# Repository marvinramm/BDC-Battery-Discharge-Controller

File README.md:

# BDC – Battery Discharge Controller

**Brings charged Li-Po and Li-Ion packs (2S–6S) down to storage voltage quickly. You set the target voltage per cell on the device. The BDC switches the load and stops on its own when the target is reached. An ESP32 runs its own firmware, BDC OS: it shows the progress on an OLED and streams it over Bluetooth LE.**

In RC model building, packs are often charged and then not used. A full Li-Po left for days ages fast; it should sit at about 3.8 V per cell. Most chargers discharge with only a few watts. The BDC uses a real load instead and gets a pack to storage voltage much faster. The first revision carried that load on the board. The second one switches any external load up to 15 A.

## Features

- **2S to 6S Li-Po / Li-Ion:** the number of cells is detected from the pack voltage at start-up.
- **Adjustable target voltage:**
  - 3.60–3.90 V per cell in 0.05 V steps, 3.75 V by default
  - the load switches off automatically when the target is reached
- **Accurate measurement:**
  - the load is switched off briefly for every reading, so the voltage drop under load does not falsify the result
  - the ADC is linearised with a calibration table
- **One-button operation (REV2):**
  - short press changes the target voltage
  - long press starts or stops the discharge
  - an RGB LED shows the state: idle, discharging, done
- **0.96" OLED:**
  - cell voltage, pack voltage, distance to the target, progress in percent
  - Bluetooth status and the detected cell count
- **Bluetooth LE:** all values are sent as notifications, so a phone app can show the progress.
- **Buzzer** when the pack is done, then **light sleep** after one minute without input.

## How it works

```mermaid
flowchart LR
    BAT["Battery<br/>2S–6S"] -- XT60 --> SW["P-MOSFET switch<br/>AOD403"]
    SW -- XT60 --> LOAD["External load<br/>up to 15 A"]
    BAT --> DIV["Voltage divider"] --> ESP["ESP32<br/>BDC OS"]
    BAT --> LDO["LM2937<br/>3.3 V"] --> ESP
    ESP -- DISCHARGE_ON --> SW
    ESP <--> OLED["OLED<br/>I²C"]
    BTN["Button"] --> ESP
    ESP --> UI["RGB LED · buzzer"]
    ESP <-. BLE .-> APP["Phone"]
```

The ESP32 measures the pack voltage through a voltage divider and averages 100 samples. During the reading it switches the load off for a moment. BDC OS converts the reading to a voltage with a measured calibration table and divides it by the detected number of cells. As long as the average cell voltage is above the target, the MOSFET stays on. When it drops 20 mV below the target, the BDC switches off, beeps and shows "Done".

## Revisions

| | REV1 (2022) | REV2 (2023) |
|---|---|---|
| **Concept** | All-in-one: load, balancer and cell monitoring on one board | Compact controller that switches an external load |
| **Load** | 100 W / 8 Ω aluminium resistor on the board, cooled by a 40 mm fan | Any load on the second XT60 connector, up to 15 A |
| **Balancing** | Six HY2213 balancer channels with 62 Ω bleed resistors | – |
| **Measurement** | Every cell via the balancer connector and a CD74HC4067 multiplexer; current and power with an INA219 and a 10 mΩ shunt | Pack voltage via voltage divider |
| **Operation** | Rotary encoder with push button | One button |
| **Connectors** | XT60, XT30, balancer connector (up to 6S), fuse holders | 2 × XT60 |
| **Board** | 100.4 × 89.4 mm | 76.7 × 38.9 mm |
| **Firmware** | [BDC OS 0.4](firmware/BDC-OS-REV1) (prototype) | [BDC OS 0.5.3](firmware/BDC-OS) |

With a fixed 8 Ω resistor, the discharge current of REV1 depends on the pack voltage: about 1 A at 2S, about 3 A at 6S. For large packs that is slow, and the resistor needs active cooling. REV2 leaves out the load. You connect whatever fits the pack, e.g. a power resistor or an electronic load. The board itself becomes small enough for a 3D-printed or acrylic case.

## Repository layout

```
firmware/BDC-OS/          BDC OS 0.5.3 for REV2 (Arduino sketch)
firmware/BDC-OS-REV1/     BDC OS 0.4 for REV1 (prototype)
hardware/bdc-rev1/        Schematic (PDF), BOM, ESP32 pin assignment, EAGLE source
hardware/bdc-rev2/        Schematic (PDF), BOM, ESP32 pin assignment, EAGLE source
hardware/mechanical/      3D-printed parts
docs/images/              Pictures used in this README
```

Gerber files and ready-to-flash firmware images are attached to the [releases](https://github.com/marvinramm/BDC/releases). Libraries, build settings and the Bluetooth interface are described in [`firmware/README.md`](firmware/README.md).

> [!WARNING]
> The BDC handles batteries that can deliver very high currents. Fuse the battery line, watch the temperature of the load and never leave a discharging pack unattended.

## License

© 2022–2023 Marvin Ramm. Open source with attribution:

- Code (`firmware/`): [MIT](LICENSE)
- Hardware and documentation: [CC BY 4.0](hardware/LICENSE)

Commercial use is allowed. Credit "BDC by Marvin Ramm" with a link to this repository. Details are in [LICENSING.md](LICENSING.md).

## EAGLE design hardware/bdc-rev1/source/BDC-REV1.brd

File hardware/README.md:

# Hardware

| Folder | Content |
|---|---|
| [`bdc-rev1`](bdc-rev1) | REV1 (2022): schematic (PDF, 2 sheets), BOM, ESP32 pin assignment, EAGLE schematic and board in `source/` |
| [`bdc-rev2`](bdc-rev2) | REV2 (2023): schematic (PDF), BOM, ESP32 pin assignment, EAGLE schematic and board in `source/` |
| [`mechanical`](mechanical) | `encoder_knob_rev1.stl` for the rotary encoder of REV1, `protection_cap.stl` |

The Gerber, drill and pick-and-place files of both revisions are attached to the [releases](https://github.com/marvinramm/BDC/releases).

- **REV2:** the files come from the EAGLE CAM processor.
- **REV1:** no CAM output was left, so the files were generated from the EAGLE board with KiCad's EAGLE importer. Check them in a Gerber viewer before you order.

The EAGLE files use parts from my own libraries. EAGLE embeds them in the `.sch` / `.brd` files, so the designs open without the libraries.

## REV1 – all-in-one

Battery input via XT60 and balancer connector (up to 6S). Each cell has an HY2213 balancer IC that switches a 62 Ω bleed resistor. The cell voltages go through dividers to a CD74HC4067 multiplexer and on to the ESP32 ADC. An INA219 measures current and power across a 10 mΩ shunt. An AOD403 P-MOSFET switches the 100 W / 8 Ω aluminium resistor on top of the board, and a 40 mm fan cools it.

## REV2 – controller for an external load

Battery and load each connect to an XT60 (`OUTPUT 15A` on the silkscreen). An AOD403 P-MOSFET, driven by an SI2302, switches the load on the high side. An LM2937 supplies the ESP32 with 3.3 V. The pack voltage reaches GPIO39 through a voltage divider. Operation is with one button, RGB LED, buzzer and 0.96" OLED.

## License

The hardware design files and documentation are licensed under [CC BY 4.0](LICENSE). See [LICENSING.md](../LICENSING.md) for the attribution text.

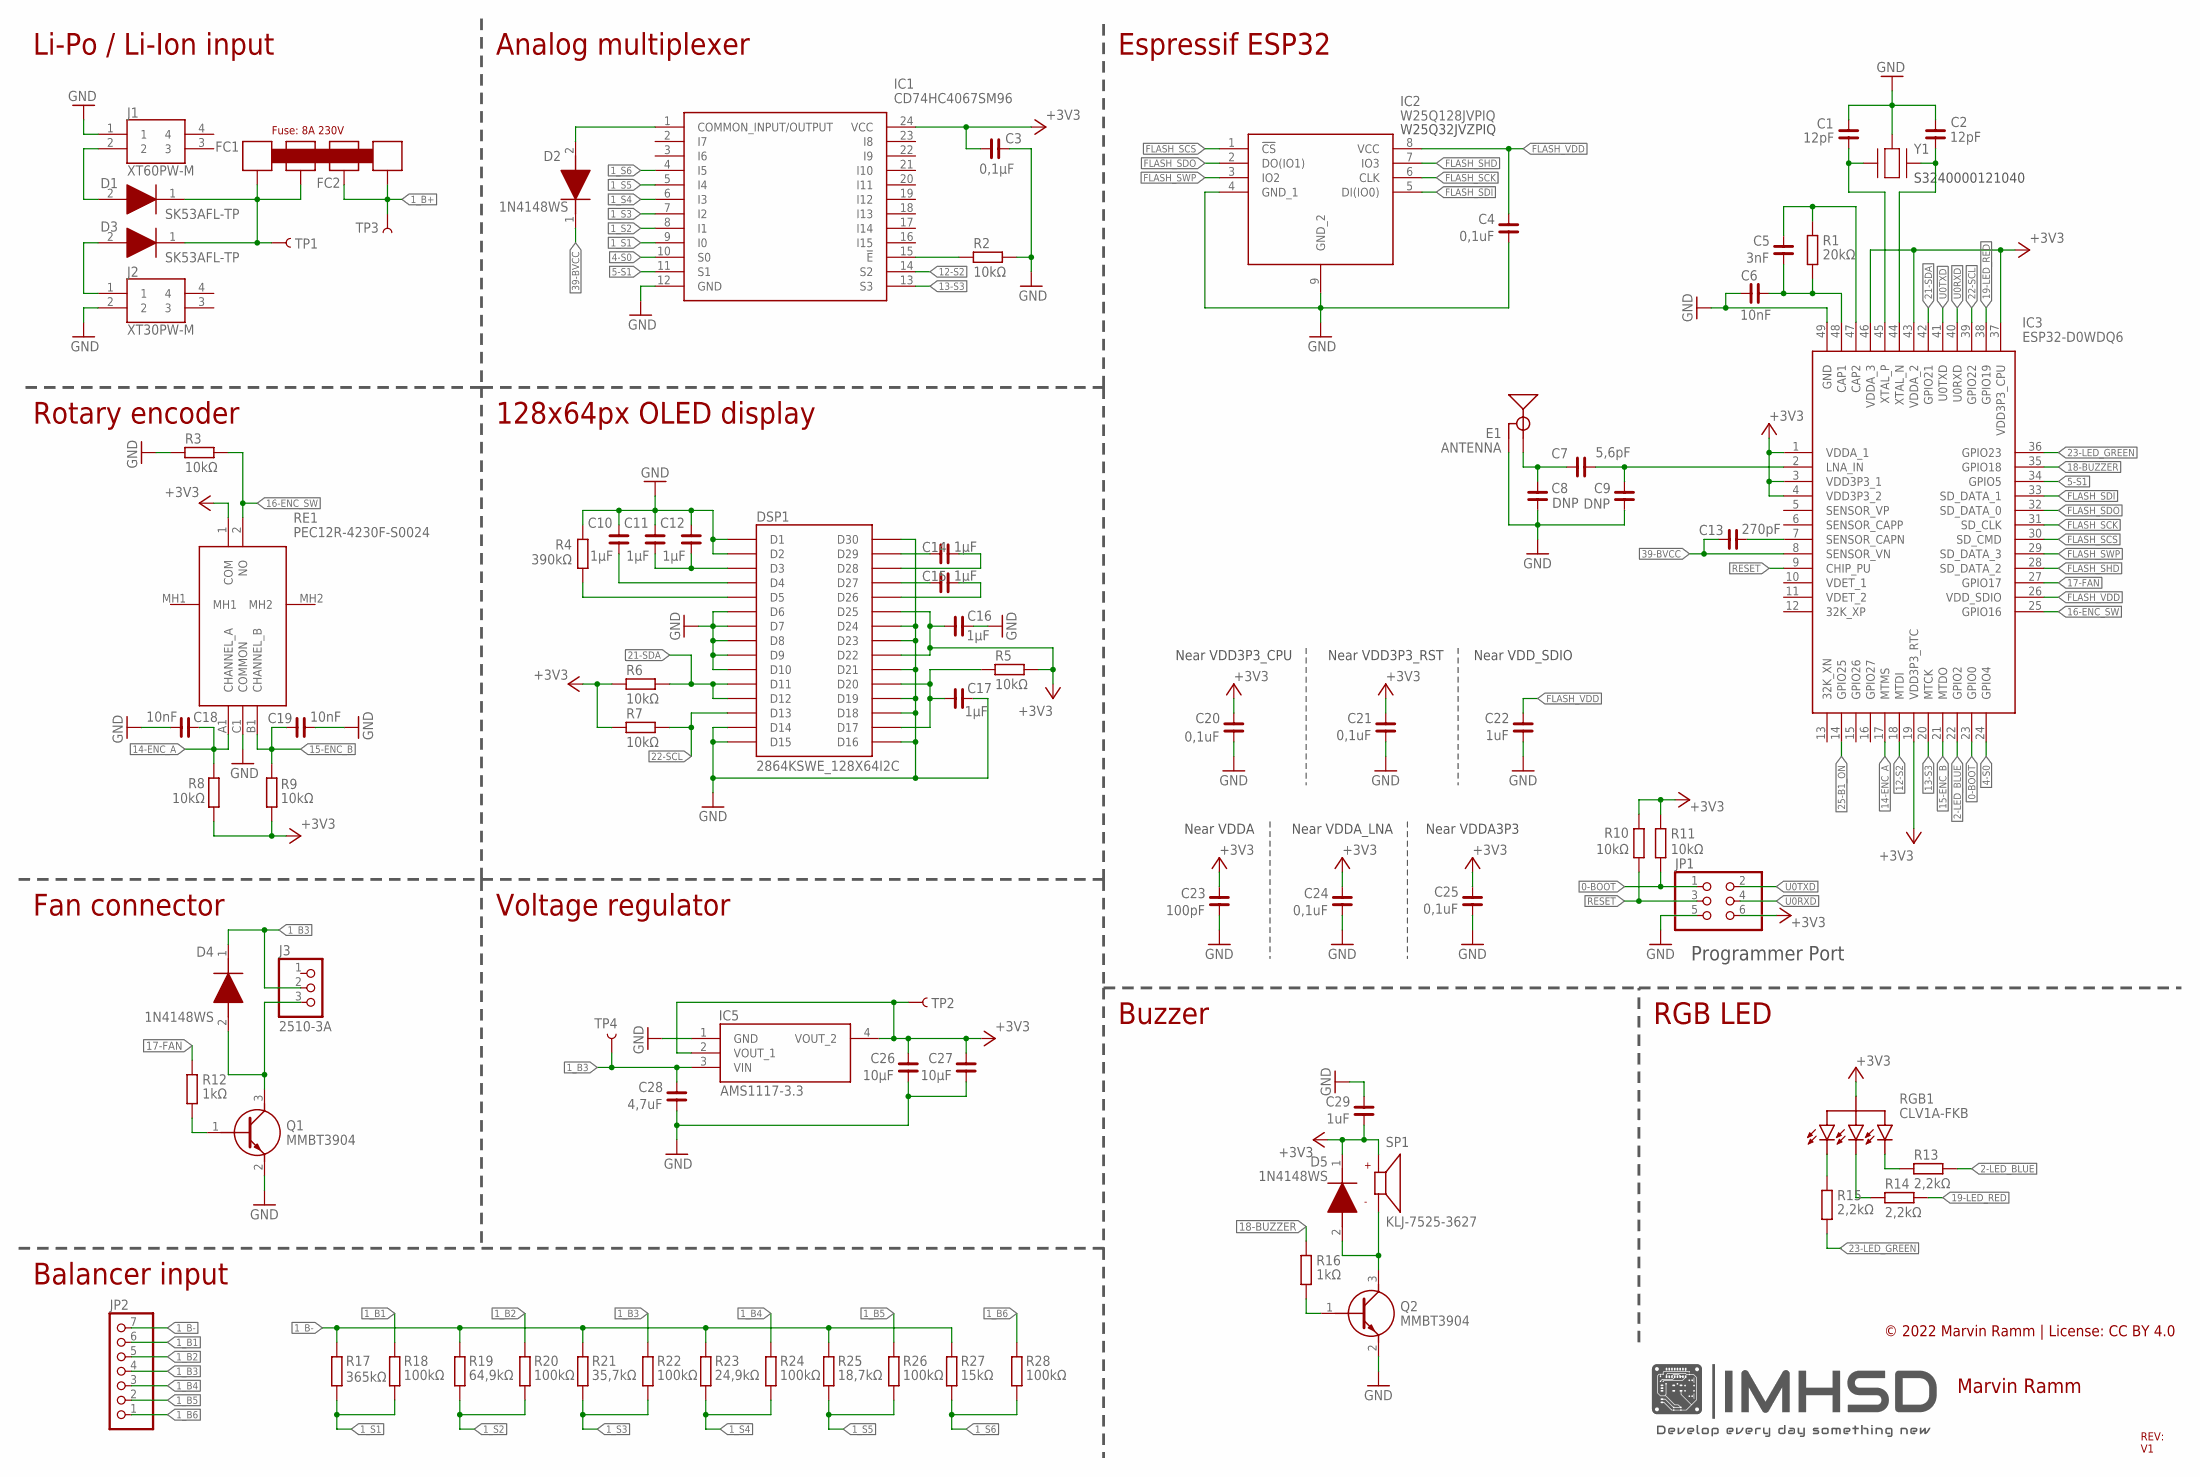
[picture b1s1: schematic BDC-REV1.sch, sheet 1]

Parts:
C1, C2: 12pF; C0402
C3: 0,1µF; C0402
C4, C20, C21, C24, C25: 0,1uF; C0402
C5: 3nF; C0402
C6, C18, C19: 10nF; C0402
C7: 5,6pF; C0402
C8, C9: DNP; C0402
C10, C11, C12, C14, C15, C16, C17: 1µF; C0402
C13: 270pF; C0402
C22, C29: 1uF; C0402
C23: 100pF; C0402
C26, C27: 10µF; C0603
C28: 4,7uF; C0402
D1, D3: SK53AFL-TP; SODFL5026X120N
D2, D4, D5: 1N4148WS; SODFL2512X90N
DSP1: 2864KSWE_128X64I2C
E1: ANTENNA; TRACE_ANTENNA_2.4GHZ_25.7MM_TUNED
FC1, FC2: FUSECLIPS; FUSECLIP
IC1: CD74HC4067SM96; SOP65P780X200-24N
IC2: W25Q128JVPIQ; SON127P800X600X80-9N
IC3: ESP32-D0WDQ6; QFN40P600X600X90-49N
IC5: AMS1117-3.3; SOT229P700X180-4N
J1: XT60PW-M; XT60PWM
J2: XT30PW-M; XT30PWM
J3: 2510-3A
JP1: PINHD-2X3; 2X03
JP2: PINHD-1X7/90; 1X07/90
Q1, Q2: MMBT3904; SOT95P240X120-3N
R1: 20kΩ; R0402
R2, R3, R5, R6, R7, R8, R9, R10, R11: 10kΩ; R0402
R4: 390kΩ; R0402
R12, R16: 1kΩ; R0402
R13, R14, R15: 2,2kΩ; R0402
R17: 365kΩ; R0402
R18, R20, R22, R24, R26, R28: 100kΩ; R0402
R19: 64,9kΩ; R0402
R21: 35,7kΩ; R0402
R23: 24,9kΩ; R0402
R25: 18,7kΩ; R0402
R27: 15kΩ; R0402
RE1: PEC12R-4230F-S0024; PEC12R4230FS0024
RGB1: RGBLED
SP1: CMT-7525-80-SMT-TR; XDCR_CMT-7525-80-SMT-TR
TP1, TP2, TP3, TP4: TEST-POINT3X5; PAD.03X.05
U$1: 40MMFAN
Y1: SMD-3225_4P16MHZ_20PF_10PPM_-4; SMD3225_4P16MHZ20PF10PPM4085

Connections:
0-BOOT: IC3.23 (GPIO0), JP1.1, R11.2
1_B1: JP2.6, R18.1; also elsewhere on the board
1_B2: JP2.5, R20.1; also elsewhere on the board
1_B3: C28.2, D4.1 (K), IC5.3 (VIN), J3.2, JP2.4, R22.1, TP4.P$1; also elsewhere on the board
1_B4: JP2.3, R24.1; also elsewhere on the board
1_B5: JP2.2, R26.1; also elsewhere on the board
1_B6: JP2.1, R28.1; also elsewhere on the board
1_B+: FC2.P1, FC2.P2, TP3.P$1; also elsewhere on the board
1_B-: JP2.7, R17.1, R19.1, R21.1, R23.1, R25.1, R27.1; also elsewhere on the board
1_S1: IC1.9 (I0), R17.2, R18.2
1_S2: IC1.8 (I1), R19.2, R20.2
1_S3: IC1.7 (I2), R21.2, R22.2
1_S4: IC1.6 (I3), R23.2, R24.2
1_S5: IC1.5 (I4), R25.2, R26.2
1_S6: IC1.4 (I5), R27.2, R28.2
2-LED_BLUE: IC3.22 (GPIO2), R13.2
4-S0: IC1.10 (S0), IC3.24 (GPIO4)
5-S1: IC1.11 (S1), IC3.34 (GPIO5)
12-S2: IC1.14 (S2), IC3.18 (MTDI)
13-S3: IC1.13 (S3), IC3.20 (MTCK)
14-ENC_A: C18.1, IC3.17 (MTMS), R8.2, RE1.A1 (CHANNEL_A)
15-ENC_B: C19.1, IC3.21 (MTDO), R9.2, RE1.B1 (CHANNEL_B)
16-ENC_SW: IC3.25 (GPIO16), R3.2, RE1.2 (NO)
17-FAN: IC3.27 (GPIO17), R12.1
18-BUZZER: IC3.35 (GPIO18), R16.1
19-LED_RED: IC3.38 (GPIO19), R14.2
21-SDA: DSP1.D11, DSP1.D12, IC3.42 (GPIO21), R6.2; also elsewhere on the board
22-SCL: DSP1.D13, IC3.39 (GPIO22), R7.2; also elsewhere on the board
23-LED_GREEN: IC3.36 (GPIO23), R15.2
25-B1_ON: IC3.14 (GPIO25); also elsewhere on the board
39-BVCC: C13.1, D2.1 (K), IC3.8 (SENSOR_VN)
+3V3: C3.1, C16.1, C20.2, C21.2, C23.2, C24.2, C25.2, C26.1, C27.1, C29.1, D5.1 (K), DSP1.D22, DSP1.D25, IC1.24 (VCC), IC3.1 (VDDA_1), IC3.3 (VDD3P3_1), IC3.4 (VDD3P3_2), IC3.19 (VDD3P3_RTC), IC3.37 (VDD3P3_CPU), IC3.43 (VDDA_2), IC3.46 (VDDA_3), IC5.2 (VOUT_1), IC5.4 (VOUT_2), JP1.6, R5.2, R6.1, R7.1, R8.1, R9.1, R10.2, R11.1, RE1.1 (COM), RGB1.+5V, SP1.P, TP2.P$1; also elsewhere on the board
FLASH_SCK: IC2.6 (CLK), IC3.31 (SD_CLK)
FLASH_SCS: IC2.1 (!CS), IC3.30 (SD_CMD)
FLASH_SDI: IC2.5 (DI(IO0)), IC3.33 (SD_DATA_1)
FLASH_SDO: IC2.2 (DO(IO1)), IC3.32 (SD_DATA_0)
FLASH_SHD: IC2.7 (IO3), IC3.28 (SD_DATA_2)
FLASH_SWP: IC2.3 (IO2), IC3.29 (SD_DATA_3)
FLASH_VDD: C4.2, C22.2, IC2.8 (VCC), IC3.26 (VDD_SDIO)
GND: C1.1, C2.1, C3.2, C4.1, C6.1, C8.1, C9.1, C10.1, C11.1, C12.1, C16.2, C17.2, C18.2, C19.2, C20.1, C21.1, C22.1, C23.1, C24.1, C25.1, C26.2, C27.2, C28.1, C29.2, DSP1.D1, DSP1.D2, DSP1.D6, DSP1.D7, DSP1.D8, DSP1.D9, DSP1.D10, DSP1.D14, DSP1.D15, DSP1.D16, DSP1.D18, DSP1.D19, DSP1.D21, DSP1.D23, DSP1.D24, DSP1.D30, E1.GND, E1.GND2 (GND), IC1.12 (GND), IC2.4 (GND_1), IC2.9 (GND_2), IC3.49 (GND), IC5.1 (GND), J1.1, J2.2, JP1.5, Q1.2 (E), Q2.2 (E), R2.2, R3.1, R4.2, RE1.C1 (COMMON), Y1.2 (GND_2), Y1.4 (GND_2); also elsewhere on the board
unnamed: D3.2 (A), J2.1
unnamed: IC1.15 (!E), R2.1
unnamed: D4.2 (A), J3.3, Q1.3 (C)
unnamed: Q1.1 (B), R12.2
unnamed: C7.1, C9.2, IC3.2 (LNA_IN)
unnamed: C5.1, C6.2, IC3.48 (CAP1), R1.2
unnamed: C5.2, IC3.47 (CAP2), R1.1
unnamed: C2.2, IC3.44 (XTAL_N), Y1.3 (CRYSTAL_2)
unnamed: C1.2, IC3.45 (XTAL_P), Y1.1 (CRYSTAL_1)
unnamed: C15.1, DSP1.D27
unnamed: C7.2, C8.2, E1.ANT (SIGNAL)
unnamed: C17.1, DSP1.D17, DSP1.D20, R5.1
unnamed: C10.2, DSP1.D4
unnamed: C15.2, DSP1.D26
unnamed: C11.2, C12.2, DSP1.D3
unnamed: DSP1.D5, R4.1
unnamed: C14.1, DSP1.D29
unnamed: C14.2, DSP1.D28
unnamed: C13.2, IC3.7 (SENSOR_CAPN)
unnamed: D1.2 (A), J1.2
unnamed: D1.1 (K), D3.1 (K), FC1.P1, FC1.P2, TP1.P$1
unnamed: D2.2 (A), IC1.1 (COMMON_INPUT/OUTPUT)
unnamed: D5.2 (A), Q2.3 (C), SP1.N
unnamed: Q2.1 (B), R16.2
unnamed: R15.1, RGB1.P3
unnamed: R13.1, RGB1.P1
unnamed: R14.1, RGB1.P2
RESET: IC3.9 (CHIP_PU), JP1.3, R10.1
U0RXD: IC3.40 (U0RXD), JP1.4
U0TXD: IC3.41 (U0TXD), JP1.2

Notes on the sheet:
Fuse: 8A 230V
FC1
FC2
KLJ-7525-3627
S3240000121040
Near VDDA
Near VDDA_LNA
Near VDDA3P3
Near VDD3P3_CPU
Near VDD3P3_RST
Near VDD_SDIO
Programmer Port
W25Q32JVZPIQ
RGB1
CLV1A-FKB
Marvin Ramm
REV: V1
© 2022 Marvin Ramm | License: CC BY 4.0
Fan connector
Rotary encoder
128x64px OLED display
Li-Po / Li-Ion input
Analog multiplexer
Espressif ESP32
Voltage regulator
Balancer input
Buzzer
RGB LED

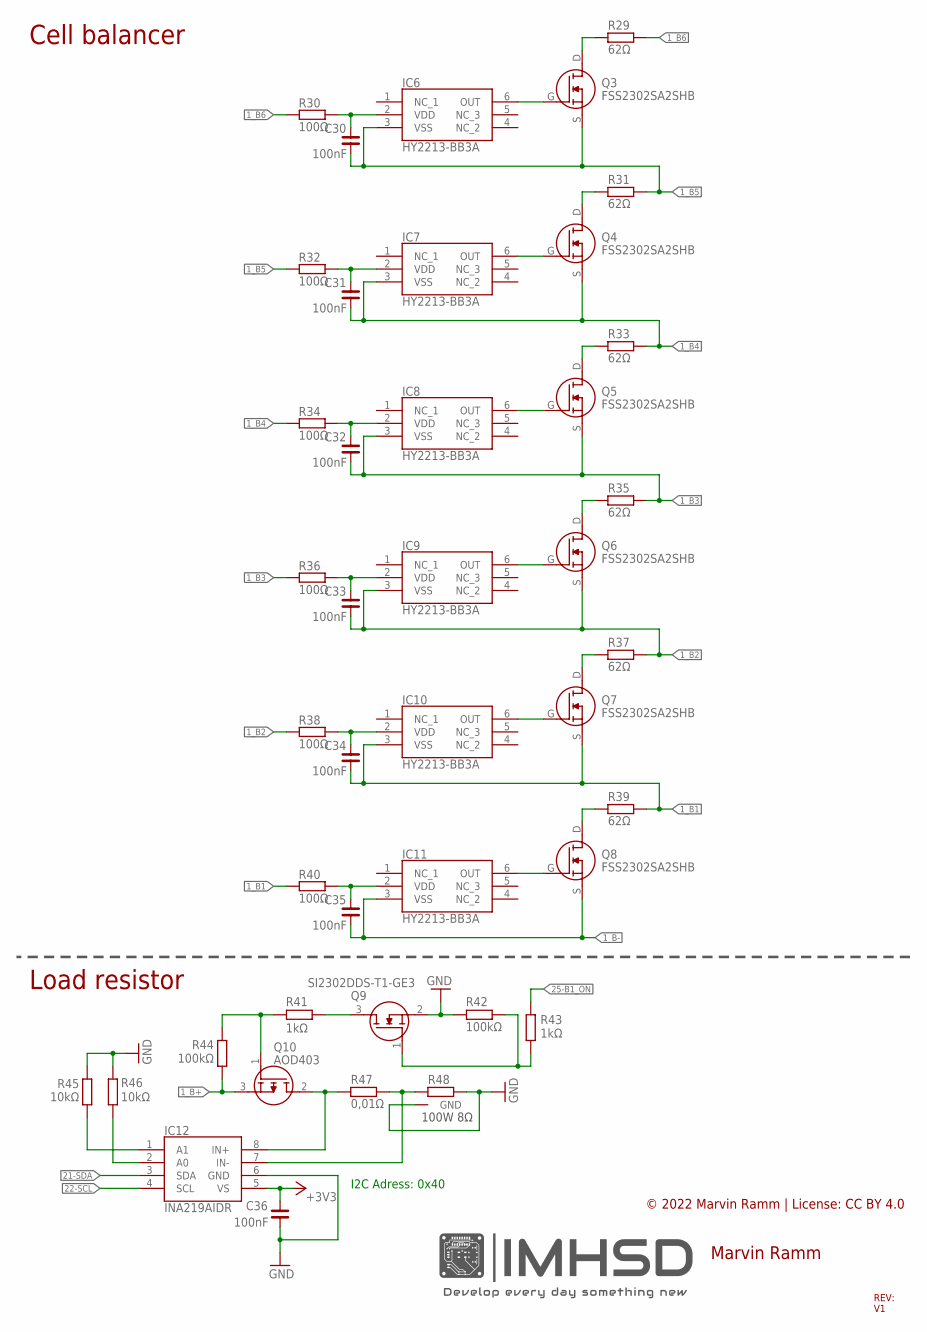
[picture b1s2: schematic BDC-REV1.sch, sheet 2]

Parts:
C30, C31, C32, C33, C34, C35, C36: 100nF; C0402
IC6, IC7, IC8, IC9, IC10, IC11: HY2213-BB3A; SOT95P280X140-6N
IC12: INA219AIDR; SOIC127P600X175-8N
Q3, Q4, Q5, Q6, Q7, Q8: FSS2302SA2SHB
Q9: SI2302DDS-T1-GE3; SOT95P237X112-3N
Q10: AOD403; AOD480
R29, R31, R33, R35, R37, R39: 62Ω; R2512
R30, R32, R34, R36, R38, R40: 100Ω; R0402
R41, R43: 1kΩ; R0402
R42, R44: 100kΩ; R0402
R45, R46: 10kΩ; R0402
R47: 0,01Ω; R2512
R48: RX24; RX24_100W

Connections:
1_B1: C34.2, IC10.3 (VSS), Q7.S, R39.2, R40.1; also elsewhere on the board
1_B2: C33.2, IC9.3 (VSS), Q6.S, R37.2, R38.1; also elsewhere on the board
1_B3: C32.2, IC8.3 (VSS), Q5.S, R35.2, R36.1; also elsewhere on the board
1_B4: C31.2, IC7.3 (VSS), Q4.S, R33.2, R34.1; also elsewhere on the board
1_B5: C30.2, IC6.3 (VSS), Q3.S, R31.2, R32.1; also elsewhere on the board
1_B6: R29.2, R30.1; also elsewhere on the board
1_B+: Q10.3 (S), R44.1; also elsewhere on the board
1_B-: C35.2, IC11.3 (VSS), Q8.S; also elsewhere on the board
21-SDA: IC12.3 (SDA); also elsewhere on the board
22-SCL: IC12.4 (SCL); also elsewhere on the board
25-B1_ON: R43.1; also elsewhere on the board
+3V3: C36.1, IC12.5 (VS); also elsewhere on the board
GND: C36.2, IC12.6 (GND), Q9.2 (S), R42.2, R45.1, R46.1, R48.2, R48.GND, R48.GND2 (GND), R48.GND3 (GND); also elsewhere on the board
unnamed: Q8.D, R39.1
unnamed: IC11.6 (OUT), Q8.G
unnamed: Q7.D, R37.1
unnamed: C35.1, IC11.2 (VDD), R40.2
unnamed: IC10.6 (OUT), Q7.G
unnamed: C34.1, IC10.2 (VDD), R38.2
unnamed: Q6.D, R35.1
unnamed: IC9.6 (OUT), Q6.G
unnamed: C33.1, IC9.2 (VDD), R36.2
unnamed: Q5.D, R33.1
unnamed: IC8.6 (OUT), Q5.G
unnamed: C32.1, IC8.2 (VDD), R34.2
unnamed: Q4.D, R31.1
unnamed: IC7.6 (OUT), Q4.G
unnamed: C31.1, IC7.2 (VDD), R32.2
unnamed: Q3.D, R29.1
unnamed: IC6.6 (OUT), Q3.G
unnamed: C30.1, IC6.2 (VDD), R30.2
unnamed: Q10.1 (G), R41.2, R44.2
unnamed: IC12.8 (IN+), Q10.2 (D), R47.1
unnamed: IC12.1 (A1), R45.2
unnamed: IC12.7 (IN-), R47.2, R48.1
unnamed: Q9.3 (D), R41.1
unnamed: Q9.1 (G), R42.1, R43.2
unnamed: IC12.2 (A0), R46.2

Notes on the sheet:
Marvin Ramm
REV: V1
© 2022 Marvin Ramm | License: CC BY 4.0
I2C Adress: 0x40
100W 8Ω
Load resistor
Cell balancer

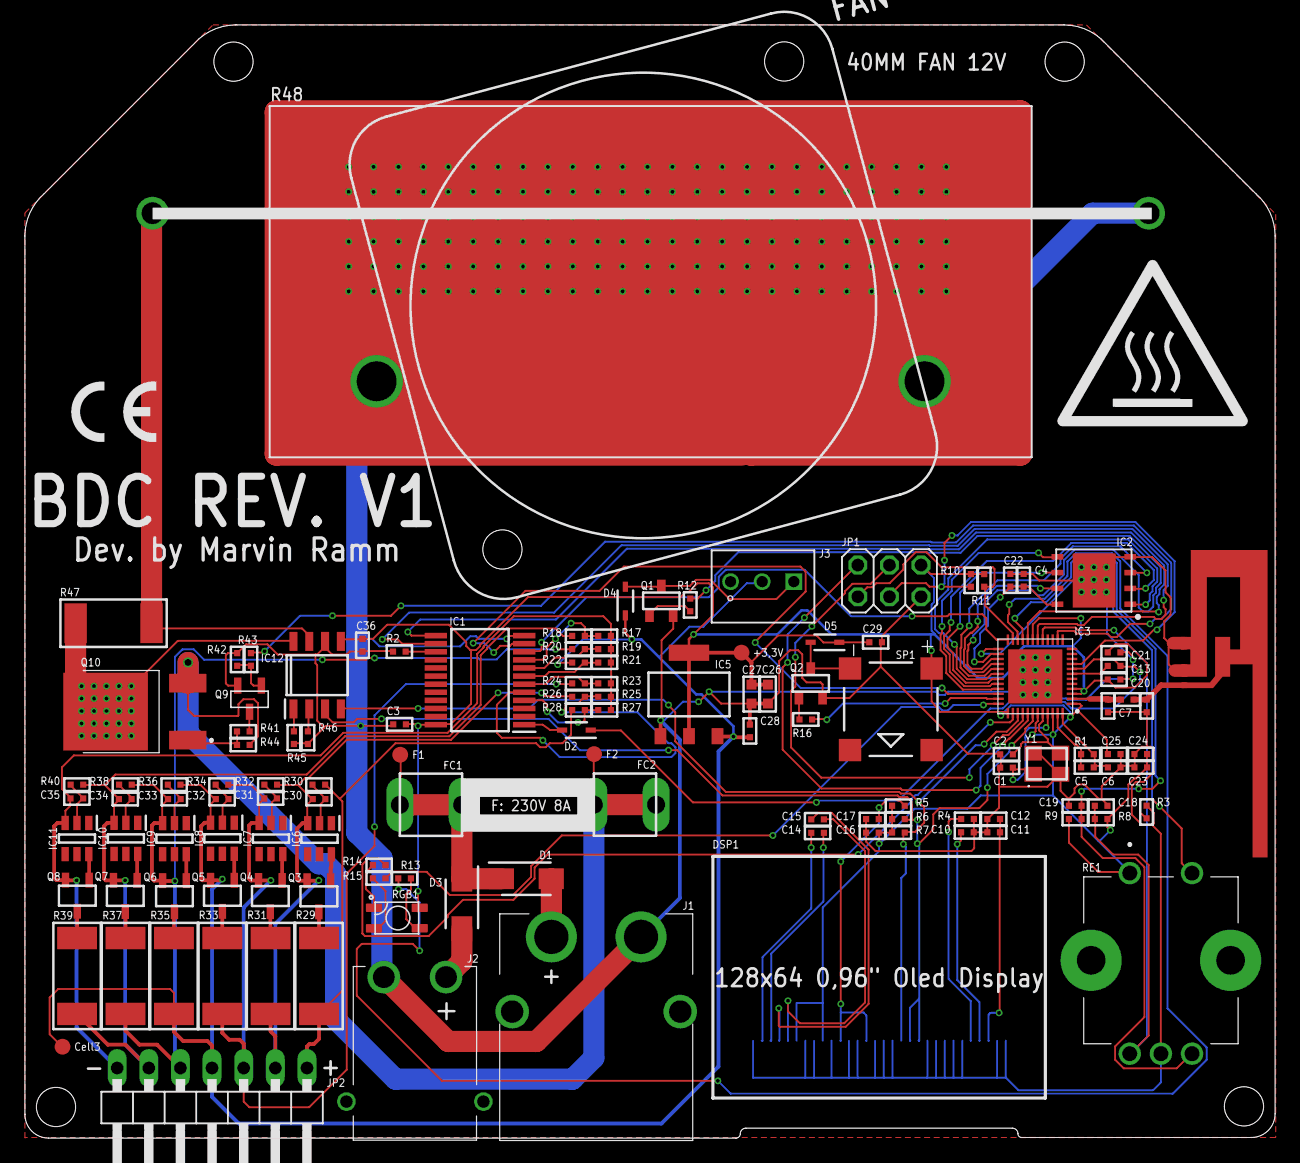
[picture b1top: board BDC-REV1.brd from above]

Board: 2 copper layers, 100.4 x 89.4 mm, 128 parts (1 on the bottom side), 95 nets.

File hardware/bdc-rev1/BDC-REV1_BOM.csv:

designators,value,package,manufacturer_part,lcsc,qty
C1 C2,12pF,C0402,,,2
C3,0.1µF,C0402,,,1
C4 C20 C21 C24 C25,0.1µF,C0402,,,5
C5,3nF,C0402,,,1
C6 C18 C19,10nF,C0402,,,3
C7,5.6pF,C0402,,,1
C8 C9,DNP,C0402,do not populate,,2
C10 C11 C12 C14 C15 C16 C17,1µF,C0402,,,7
C13,270pF,C0402,,,1
C22 C29,1µF,C0402,,,2
C23,100pF,C0402,,,1
C26 C27,10µF,C0603,,,2
C28,4.7µF,C0402,,,1
C30 C31 C32 C33 C34 C35 C36,100nF,C0402,,,7
D1 D3,,SODFL5026X120N,SK53AFL-TP,,2
D2 D4 D5,,SODFL2512X90N,1N4148WS,,3
DSP1,,2864KSWE_128X64I2C,"0.96"" OLED 128x64 I2C (2864KSWE)",,1
E1,,TRACE_ANTENNA_2.4GHZ_25.7MM_TUNED,PCB trace antenna 2.4 GHz,,1
FC1 FC2,,FUSECLIP,fuse clip 5x20 mm,,2
IC1,,SOP65P780X200-24N,CD74HC4067SM96,,1
IC2,,SON127P800X600X80-9N,W25Q128JVPIQ,,1
IC3,,QFN40P600X600X90-49N,ESP32-D0WDQ6,,1
IC5,,SOT229P700X180-4N,AMS1117-3.3,,1
IC6 IC7 IC8 IC9 IC10 IC11,,SOT95P280X140-6N,HY2213-BB3A,,6
IC12,,SOIC127P600X175-8N,INA219AIDR,,1
J1,,XT60PWM,XT60PW-M,,1
J2,,XT30PWM,XT30PW-M,,1
J3,,2510-3A,2510-3A,,1
JP1,,2X03,pin header 2x3,,1
JP2,,1X07/90,pin header 1x7 angled,,1
Q1 Q2,,SOT95P240X120-3N,MMBT3904,,2
Q3 Q4 Q5 Q6 Q7 Q8,,FSS2302SA2SHB,FSS2302SA2SHB,,6
Q9,,SOT95P237X112-3N,SI2302DDS-T1-GE3,,1
Q10,,AOD480,AOD403,,1
R1,20kΩ,R0402,,,1
R2 R3 R5 R6 R7 R8 R9 R10 R11 R45 R46,10kΩ,R0402,,,11
R4,390kΩ,R0402,,,1
R12 R16 R41 R43,1kΩ,R0402,,,4
R13 R14 R15,2.2kΩ,R0402,,,3
R17,365kΩ,R0402,,,1
R18 R20 R22 R24 R26 R28 R42 R44,100kΩ,R0402,,,8
R19,64.9kΩ,R0402,,,1
R21,35.7kΩ,R0402,,,1
R23,24.9kΩ,R0402,,,1
R25,18.7kΩ,R0402,,,1
R27,15kΩ,R0402,,,1
R29 R31 R33 R35 R37 R39,62Ω,R2512,,,6
R30 R32 R34 R36 R38 R40,100Ω,R0402,,,6
R47,0.01Ω,R2512,,,1
R48,8Ω 100W,RX24_100W,RX24 100W,,1
RE1,,PEC12R4230FS0024,PEC12R-4230F-S0024,,1
RGB1,,RGBLED,CLV1A-FKB,,1
SP1,,XDCR_CMT-7525-80-SMT-TR,CMT-7525-80-SMT-TR,,1
TP1 TP2 TP3 TP4,,PAD.03X.05,test point,,4
U$1,,40MMFAN,40 mm fan 12 V,,1
Y1,,SMD3225_4P16MHZ20PF10PPM4085,16 MHz crystal 3225 20 pF,,1

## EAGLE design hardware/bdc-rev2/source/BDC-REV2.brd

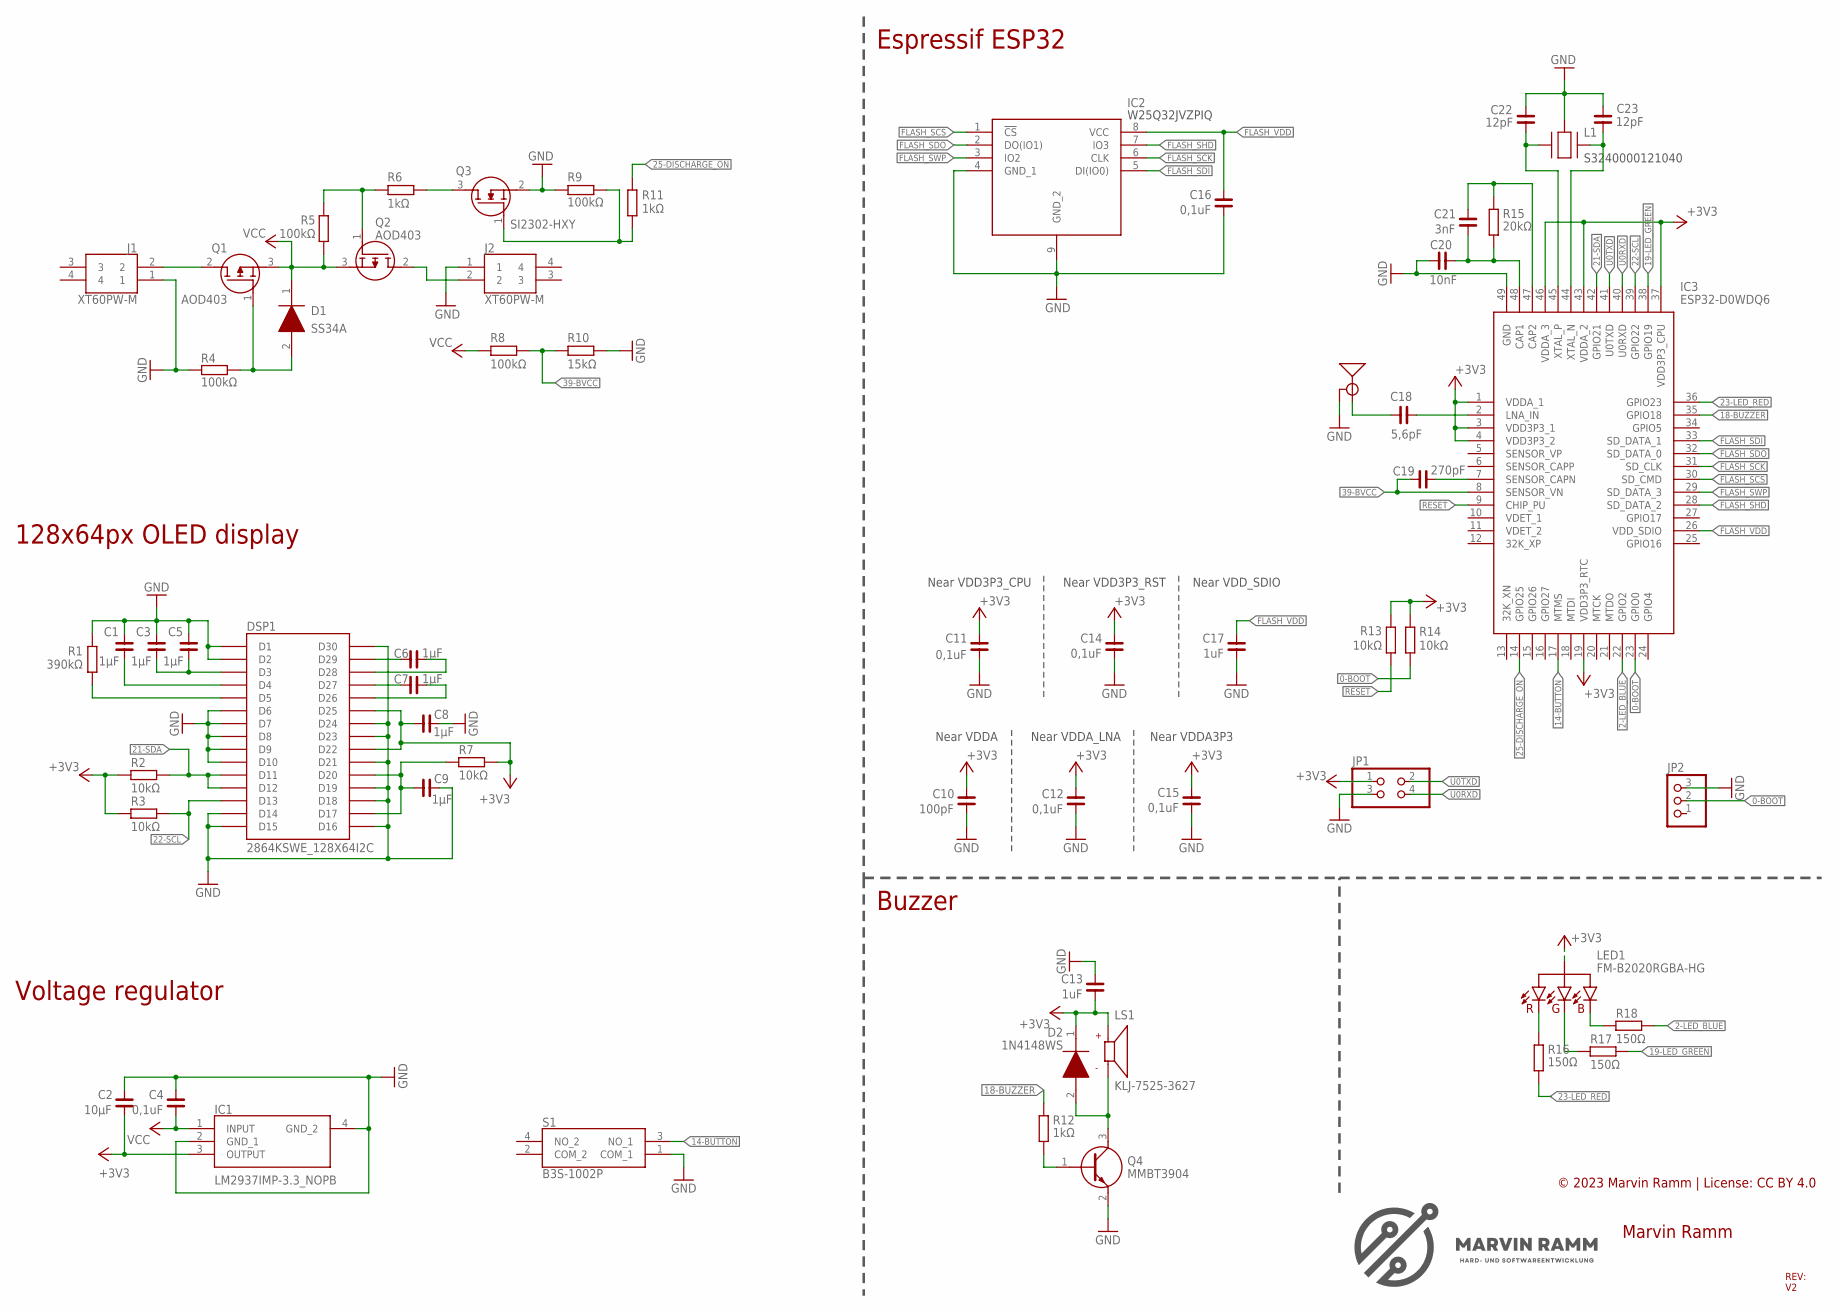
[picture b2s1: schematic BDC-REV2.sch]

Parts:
C1, C3, C5, C6, C7, C8, C9: 1µF; C0402
C2: 10µF; C0603
C4, C11, C12, C14, C15, C16: 0,1uF; C0402
C10: 100pF; C0402
C13, C17: 1uF; C0402
C18: 5,6pF; C0402
C19: 270pF; C0402
C20: 10nF; C0402
C21: 3nF; C0402
C22, C23: 12pF; C0402
D1: SS34A; DIOM5026X262N
D2: 1N4148WS; SODFL2512X90N
DSP1: 2864KSWE_128X64I2C
E1: ANTENNA-GROUNDEDTRACE-15.2MM; TRACE_ANTENNA_2.4GHZ_15.2MM
IC1: LM2937IMP-3.3_NOPB; SOT230P700X180-4N
IC2: W25Q128JVPIQ; SON127P800X600X80-9N
IC3: ESP32-D0WDQ6; QFN40P600X600X90-49N
J1, J2: XT60PW-M; XT60PWM
JP1: PINHD-2X2; 2X02
JP2: PINHD-1X3; 1X03
L1: SMD-3225_4P16MHZ_20PF_10PPM_-4; SMD3225_4P16MHZ20PF10PPM4085
LED1: FM-B2020RGBA-HG; FMB2020RGBAHG
LS1: CMT-7525-80-SMT-TR; XDCR_CMT-7525-80-SMT-TR
Q1, Q2: AOD403; AOD480
Q3: SI2302DDS-T1-GE3; SOT95P237X112-3N
Q4: MMBT3904; SOT95P240X120-3N
R1: 390kΩ; R0402
R2, R3, R7, R13, R14: 10kΩ; R0402
R4, R5, R8, R9: 100kΩ; R0402
R6, R11, R12: 1kΩ; R0402
R10: 15kΩ; R0402
R15: 20kΩ; R0402
R16, R17, R18: 150Ω; R0402
S1: B3S-1002P; B3S1002P

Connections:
0-BOOT: IC3.23 (GPIO0), JP2.2, R14.2
2-LED_BLUE: IC3.22 (GPIO2), R18.2
14-BUTTON: IC3.17 (MTMS), S1.3 (NO_1)
18-BUZZER: IC3.35 (GPIO18), R12.1
19-LED_GREEN: IC3.38 (GPIO19), R17.2
21-SDA: DSP1.D11, DSP1.D12, IC3.42 (GPIO21), R2.2
22-SCL: DSP1.D13, IC3.39 (GPIO22), R3.2
23-LED_RED: IC3.36 (GPIO23), R16.2
25-DISCHARGE_ON: IC3.14 (GPIO25), R11.1
39-BVCC: C19.1, IC3.8 (SENSOR_VN), R8.1, R10.2
+3V3: C2.2, C8.1, C10.2, C11.2, C12.2, C13.1, C14.2, C15.2, D2.1 (K), DSP1.D22, DSP1.D25, IC1.3 (OUTPUT), IC3.1 (VDDA_1), IC3.3 (VDD3P3_1), IC3.4 (VDD3P3_2), IC3.19 (VDD3P3_RTC), IC3.37 (VDD3P3_CPU), IC3.43 (VDDA_2), IC3.46 (VDDA_3), JP1.1, LED1.3 (VCC), LS1.P, R2.1, R3.1, R7.2, R13.2, R14.1
FLASH_SCK: IC2.6 (CLK), IC3.31 (SD_CLK)
FLASH_SCS: IC2.1 (!CS), IC3.30 (SD_CMD)
FLASH_SDI: IC2.5 (DI(IO0)), IC3.33 (SD_DATA_1)
FLASH_SDO: IC2.2 (DO(IO1)), IC3.32 (SD_DATA_0)
FLASH_SHD: IC2.7 (IO3), IC3.28 (SD_DATA_2)
FLASH_SWP: IC2.3 (IO2), IC3.29 (SD_DATA_3)
FLASH_VDD: C16.2, C17.2, IC2.8 (VCC), IC3.26 (VDD_SDIO)
GND: C1.1, C2.1, C3.1, C4.2, C5.1, C8.2, C9.2, C10.1, C11.1, C12.1, C13.2, C14.1, C15.1, C16.1, C17.1, C20.1, C22.1, C23.1, DSP1.D1, DSP1.D2, DSP1.D6, DSP1.D7, DSP1.D8, DSP1.D9, DSP1.D10, DSP1.D14, DSP1.D15, DSP1.D16, DSP1.D18, DSP1.D19, DSP1.D21, DSP1.D23, DSP1.D24, DSP1.D30, E1.GND, IC1.2 (GND_1), IC1.4 (GND_2), IC2.4 (GND_1), IC2.9 (GND_2), IC3.49 (GND), J1.1, J2.1, JP1.3, JP2.3, L1.2 (GND_2), L1.4 (GND_2), Q3.2 (S), Q4.2 (E), R1.2, R4.1, R9.2, R10.1, S1.1 (COM_1)
unnamed: C18.2, E1.ANT (SIGNAL)
unnamed: Q2.1 (G), R5.2, R6.2
unnamed: J2.2, Q2.2 (D)
unnamed: Q3.3 (D), R6.1
unnamed: Q3.1 (G), R9.1, R11.2
unnamed: LED1.1 (R), R16.1
unnamed: LED1.2 (B), R18.1
unnamed: LED1.4 (G), R17.1
unnamed: J1.2, Q1.2 (D)
unnamed: D1.2 (A), Q1.1 (G), R4.2
unnamed: C18.1, IC3.2 (LNA_IN)
unnamed: C20.2, C21.1, IC3.48 (CAP1), R15.2
unnamed: C21.2, IC3.47 (CAP2), R15.1
unnamed: C23.2, IC3.44 (XTAL_N), L1.3 (CRYSTAL_2)
unnamed: C22.2, IC3.45 (XTAL_P), L1.1 (CRYSTAL_1)
unnamed: C7.1, DSP1.D27
unnamed: C9.1, DSP1.D17, DSP1.D20, R7.1
unnamed: C1.2, DSP1.D4
unnamed: C7.2, DSP1.D26
unnamed: C3.2, C5.2, DSP1.D3
unnamed: DSP1.D5, R1.1
unnamed: C6.1, DSP1.D29
unnamed: C6.2, DSP1.D28
unnamed: C19.2, IC3.7 (SENSOR_CAPN)
unnamed: D2.2 (A), LS1.N, Q4.3 (C)
unnamed: Q4.1 (B), R12.2
RESET: IC3.9 (CHIP_PU), R13.1
U0RXD: IC3.40 (U0RXD), JP1.4
U0TXD: IC3.41 (U0TXD), JP1.2
VCC: C4.1, D1.1 (K), IC1.1 (INPUT), Q1.3 (S), Q2.3 (S), R5.1, R8.2

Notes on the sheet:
KLJ-7525-3627
S3240000121040
Near VDDA
Near VDDA_LNA
Near VDDA3P3
Near VDD3P3_CPU
Near VDD3P3_RST
Near VDD_SDIO
W25Q32JVZPIQ
Marvin Ramm
REV: V2
© 2023 Marvin Ramm | License: CC BY 4.0
128x64px OLED display
Espressif ESP32
Voltage regulator
Buzzer
SI2302-HXY

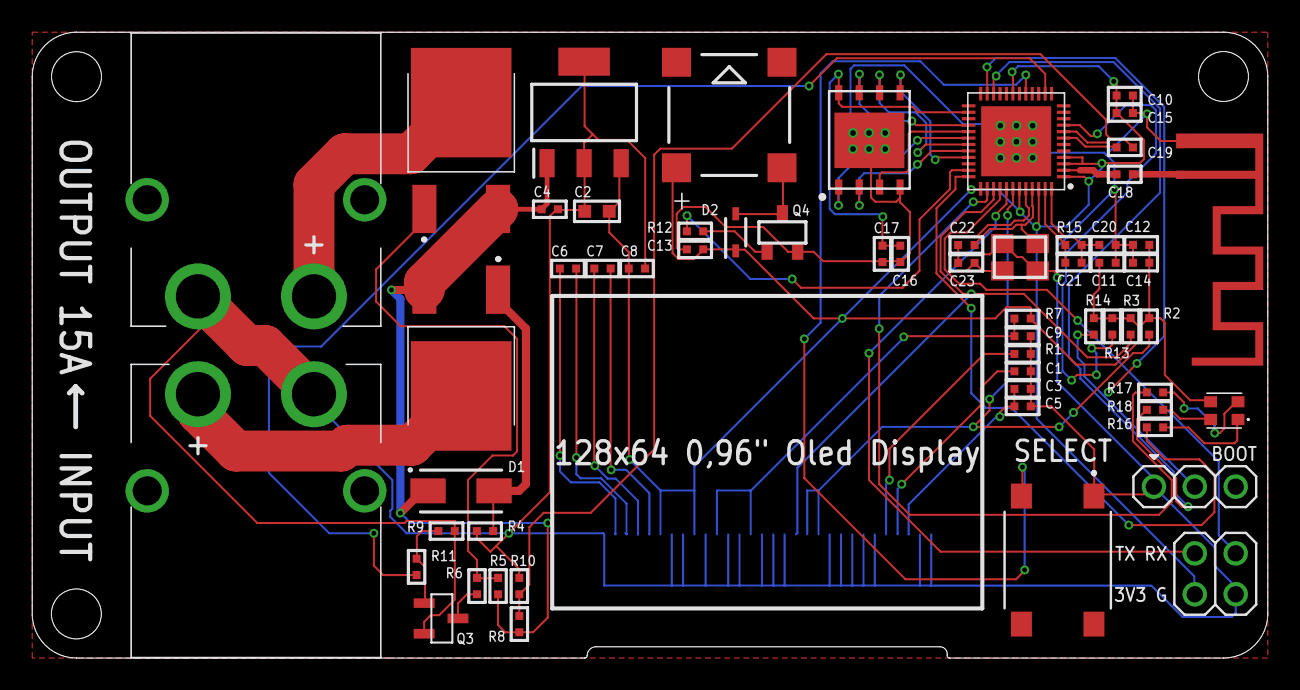
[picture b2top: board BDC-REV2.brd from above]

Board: 2 copper layers, 76.7 x 38.9 mm, 60 parts (1 on the bottom side), 49 nets.

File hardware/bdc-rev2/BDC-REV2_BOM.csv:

designators,value,package,manufacturer_part,lcsc,qty
C1 C3 C5 C6 C7 C8 C9,1µF,C0402,,,7
C2,10µF,C0603,,,1
C4 C11 C12 C14 C15 C16,0.1µF,C0402,,,6
C10,100pF,C0402,,,1
C13 C17,1µF,C0402,,,2
C18,5.6pF,C0402,,,1
C19,270pF,C0402,,,1
C20,10nF,C0402,,,1
C21,3nF,C0402,,,1
C22 C23,12pF,C0402,,,2
D1,,DIOM5026X262N,SS34A,,1
D2,,SODFL2512X90N,1N4148WS,,1
DSP1,,2864KSWE_128X64I2C,"0.96"" OLED 128x64 I2C (2864KSWE)",,1
E1,,TRACE_ANTENNA_2.4GHZ_15.2MM,PCB trace antenna 2.4 GHz,,1
IC1,,SOT230P700X180-4N,LM2937IMP-3.3_NOPB,,1
IC2,,SON127P800X600X80-9N,W25Q128JVPIQ,,1
IC3,,QFN40P600X600X90-49N,ESP32-D0WDQ6,,1
J1 J2,,XT60PWM,XT60PW-M,,2
JP1,,2X02,pin header 2x2,,1
JP2,,1X03,pin header 1x3,,1
L1,,SMD3225_4P16MHZ20PF10PPM4085,16 MHz crystal 3225 20 pF,,1
LED1,,FMB2020RGBAHG,FM-B2020RGBA-HG,,1
LS1,,XDCR_CMT-7525-80-SMT-TR,CMT-7525-80-SMT-TR,,1
Q1 Q2,,AOD480,AOD403,,2
Q3,,SOT95P237X112-3N,SI2302DDS-T1-GE3,,1
Q4,,SOT95P240X120-3N,MMBT3904,,1
R1,390kΩ,R0402,,,1
R2 R3 R7 R13 R14,10kΩ,R0402,,,5
R4 R5 R8 R9,100kΩ,R0402,,,4
R6 R11 R12,1kΩ,R0402,,,3
R10,15kΩ,R0402,,,1
R15,20kΩ,R0402,,,1
R16 R17 R18,150Ω,R0402,,,3
S1,,B3S1002P,B3S-1002P,,1

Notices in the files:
README.md:
License: MIT
parts and their libraries:
rc-master-smd: Copyright (C) 2007, Bob Starr
SparkFun-Connectors: Licensing: Creative Commons ShareAlike 4.0 International - https://creativecommons.org/licenses/by-sa/4.0
